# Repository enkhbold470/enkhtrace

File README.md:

# EnkhTrace V1.0

A line-follower robot board built around an STM32F103RET6, with a TB6612FNG
motor driver for two motors, a sensor-array header, a JDY-30 Bluetooth module,
an LY3200ALH gyro, a buzzer and status LEDs. Designed by Enkhbold Ganbold for
the Erdenet robot challenge.

| | |
|---|---|
| Size | 99.2 × 95.3 mm |
| Layers | 2 copper |
| Footprints | 82 |
| Nets | 87 |

## Files

- `hardware/enkhtrace.kicad_pcb` — the board in KiCad 10 format.
- `easyeda/enkhtrace_pcb.easyeda.json` — the original EasyEDA Standard document.
- `firmware/Src/` — the STM32 firmware (STM32CubeMX / HAL project sources).
- `images/` — a render of the top side, plus photos of the first build, the
  soldering and the bare PCB.

## Build photos

## Firmware

`firmware/Src/` holds the sources for the STM32F103RET6: `main.c` and the
STM32CubeMX-generated `stm32f1xx_hal_msp.c`, `stm32f1xx_it.c` and
`system_stm32f1xx.c`. It is the source folder only; the CubeMX project file,
the HAL/CMSIS drivers and the headers are not included, so regenerate them with
STM32CubeMX for an STM32F103RETx before building.

## Where it came from

The board was drawn in EasyEDA Standard and published on OSHWLab:
<https://oshwlab.com/enkhbold470/line-follower-for-erdenet-robot-challenge>.
It was converted with KiCad 10.0.6's EasyEDA importer and its copper pours were
refilled. With the pours filled, KiCad's DRC finds every net connected; the
remaining DRC findings are silkscreen and clearance checks against KiCad's
default rules, not the rules the board was designed to. No schematic was
published with the original project, so none is included.

## Licence

MIT — see [LICENSE](LICENSE) — for the board, the images and the code written
for this project. The STM32CubeMX-generated parts of the firmware are
© STMicroelectronics under the BSD 3-Clause licence stated in each file's
header, and those headers are kept as they were.

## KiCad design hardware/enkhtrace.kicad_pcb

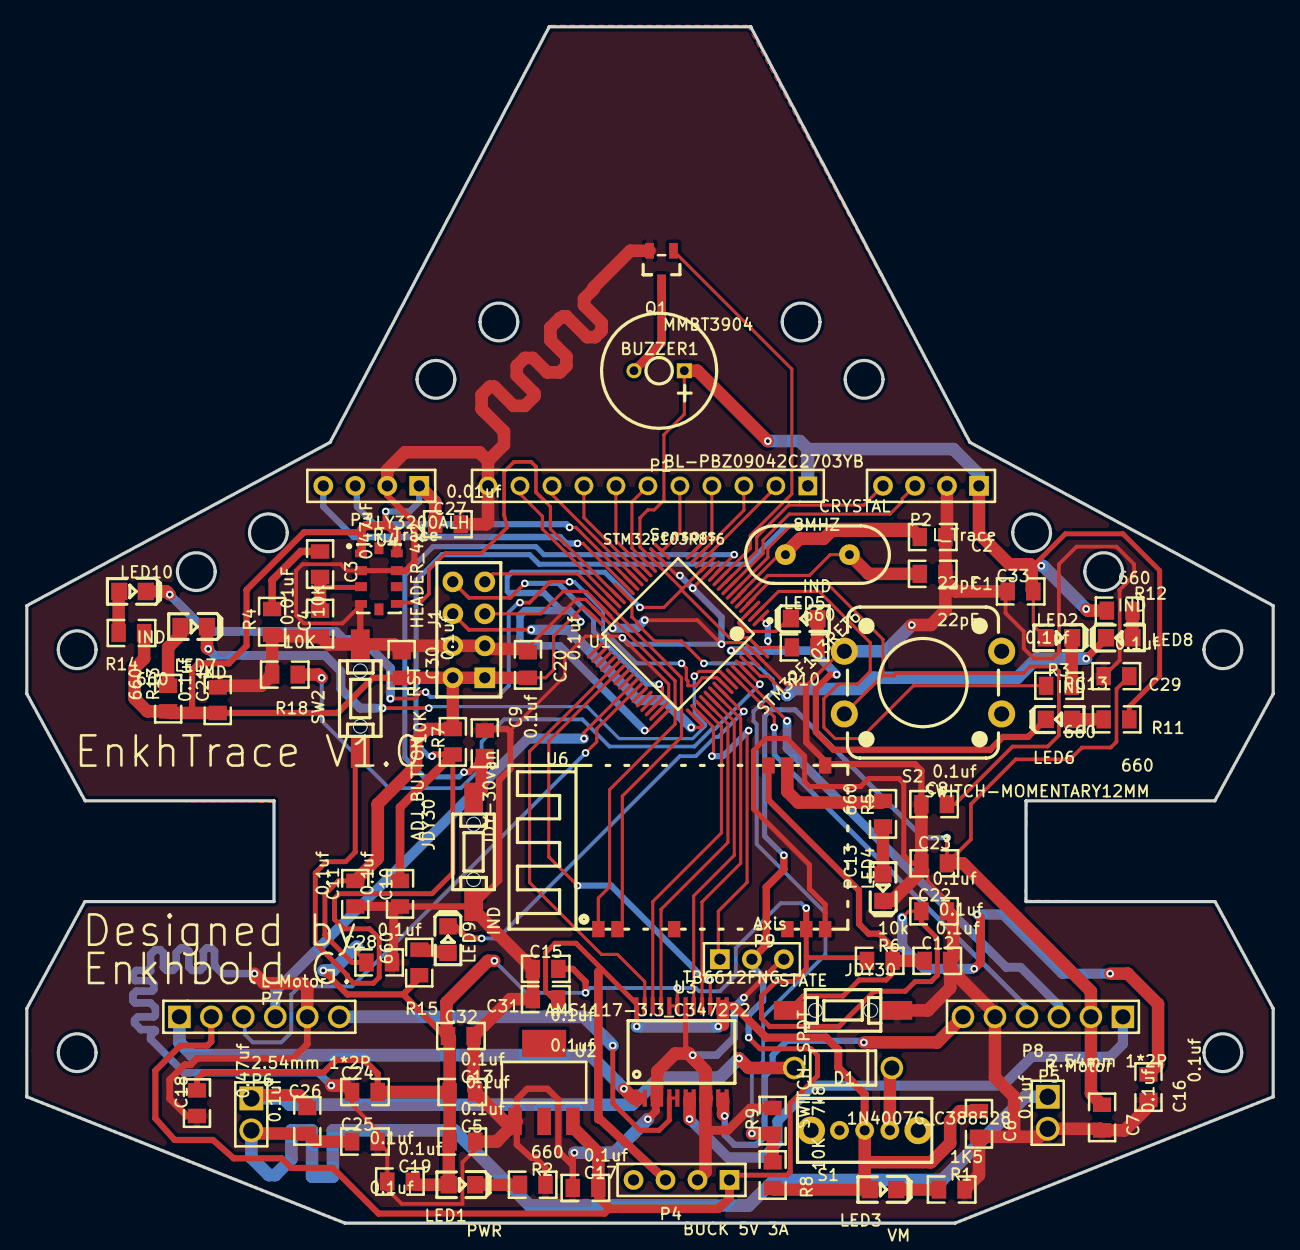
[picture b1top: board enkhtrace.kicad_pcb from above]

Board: 2 copper layers, 99.0 x 95.0 mm, 82 parts (0 on the bottom side), 70 nets.

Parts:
8MHZ: CRYSTAL; HC49US
ADJ_BUTTON: JDY30; SMD-6X3.3X5
BUZZER1: BL-PBZ09042C2703YB; BUZZER-R9.0-2P-4.0PITCH
C1, C2: 22pF; 0805
C3: 0.47uF; 0805
C4: 0.01uF; 0805
C5, C6, C7, C8, C9, C10, C11, C12, C13, C15, C16, C17, C19, C20, C21, C22, C23, C24, C25, C26, C28, C29, C30, C31, C32, C33: 0.1uf; 0805
C18: 0.47uf; 0805
C27: 0.01uf; 0805
D1: 1N4007G_C388528; DO-41_D1.20-L5.30-W2.80-L-RD
J1: HEADER_4x2; HEADER-2X4
LED1: PWR; LED-0805
LED2, LED4: PC13; LED-0805
LED3: VM; LED-0805
LED5, LED6, LED7, LED8, LED9, LED10: IND; LED-0805
P1: Sensors; HDR-11X1/2.54
P2: L_Trace; HDR-4X1/2.54
P3: R_Trace; HDR-4X1/2.54
P4: BUCK 5V 3A; HDR-4X1/2.54
P5, P6: 2.54mm 1*2P; HDR-2X1/2.54
P7: L Motor; HDR-6X1/2.54
P8: R Motor; HDR-6X1/2.54
P9: Axis; HDR-3X1/2.54
Q1: MMBT3904; SOT-23(SOT-23-3)
R1: 1K5; 0805
R2, R3, R5, R10, R11, R12, R13, R14, R15: 660; 0805
R4, R7, R8, R18: 10K; 0805
R6: 10k; 0805
R9: 7k8; 0805
S1: SWITCH-SPDT; SMD SWITCH 1234
S2: SWITCH-MOMENTARY12MM; TACTILE-PTH-12MM
STATE: JDY30; SMD-6X3.3X5
SW2: RST; SMD-6X3.3X5
U1: STM32F103RET6; LQFP-64_10X10X05P
U2: AMS1117-3.3_C347222; SOT-223
U3: TB6612FNG; SSOP24
U4: LY3200ALH; LGA10-3X5X1
U6: JDY-30van; JDY-30VAN-1.5-26.9X13.0X2.2MM

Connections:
+3V3: BUZZER1.1, C5.1, C11.2, C13.1, C15.1, C16.1, C18.1, C19.2, C20.2, C21.1, C22.1, C24.1, C27.1, C28.1, C30.2, C32.2, C33.1, J1.1, J1.2, LED1.1, LED2.1, P1.1, P2.1, P3.1, R6.1, R7.2, R10.1, R11.1, R12.1, R13.1, R14.1, R15.1, U1.1, U1.13, U1.19, U1.32, U1.48, U1.64, U3.19, U3.20, U4.1, U4.9, U6.12
+5V: C7.1, C17.2, C23.1, C29.2, P4.1, P7.2, P8.2, P9.2, U2.3
ADJ_BUTTON: ADJ_BUTTON.2, C9.2, U1.11
AIN1: U1.52, U3.21
AIN2: U1.51, U3.22
AXISPWM: P9.1, U1.50
BIN1: U1.53, U3.17
BIN2: U1.54, U3.16
BOOT0: R18.2, U1.60
BUZZ: Q1.1, U1.10
BUZZER1_2: BUZZER1.2, Q1.3
C3_1: C3.1, R4.1
GND: ADJ_BUTTON.1, C1.1, C2.1, C4.1, C5.2, C6.2, C7.2, C8.1, C9.1, C10.1, C11.1, C12.2, C13.2, C15.2, C16.2, C17.1, C18.2, C19.1, C20.1, C21.2, C22.2, C23.2, C24.2, C25.1, C27.2, C28.2, C29.1, C30.1, C31.2, C32.1, C33.2, J1.3, J1.4, LED4.2, P1.11, P2.2, P3.2, P4.2, P5.2, P7.5, P8.5, P9.3, Q1.2, R1.2, R2.2, R4.2, R9.1, R18.1, S2.1, STATE.2, SW2.1, U1.12, U1.18, U1.31, U1.47, U1.63, U2.1, U3.3, U3.4, U3.9, U3.10, U3.18, U4.2, U4.4, U4.8, U6.13, U6.22
GYROZ: U1.27, U4.6
IR: P1.10, U1.28
LCHA: P7.3, U1.42
LCHB: P7.4, U1.41
LED1: LED5.2, U1.3
LED1_2: LED1.2, R2.1
LED2: LED6.2, U1.62
LED2_2: LED2.2, R3.1
LED3: LED8.2, U1.61
LED3_2: LED3.2, R1.1
LED4: LED7.2, U1.57
LED5: LED10.2, U1.56
LED5_1: LED5.1, R10.2
LED6: LED9.2, U1.55
LED6_1: LED6.1, R11.2
LED7_1: LED7.1, R13.2
LED8_1: LED8.1, R12.2
LED9_1: LED9.1, R15.2
LED10_1: LED10.1, R14.2
ML1: P7.1, U3.1, U3.2
ML2: P7.6, U3.5, U3.6
MR1: P8.1, U3.7, U3.8
MR2: P8.6, U3.11, U3.12
P5_1: C25.2, C26.1, P5.1, P6.2
P6_1: C26.2, D1.2, P6.1
PC13: R3.2, U1.2
PWMA: U1.37, U3.23
PWMB: U1.38, U3.15
R5_1: LED4.1, R5.1
RCHA: P8.3, U1.59
RCHB: P8.4, U1.58
RST: C10.2, R7.1, SW2.2, U1.7
RX: J1.5, U1.30, U6.1
S1_2: D1.1, S1.2
SENSOR1: P1.2, U1.14
SENSOR2: P1.3, U1.15
SENSOR3: P1.4, U1.16
SENSOR4: P1.5, U1.17
SENSOR5: P1.6, U1.20
SENSOR6: P1.7, U1.21
SENSOR7: P1.8, U1.22
SENSOR8: P1.9, U1.23
START: C8.2, S2.3, U1.4
SWCLK: J1.6, U1.49
SWDIO: J1.8, U1.46
TRACE1: P2.3, U1.8
TRACE2: P2.4, U1.9
TRACE3: P3.3, U1.24
TRACE4: P3.4, U1.25
TX: J1.7, U1.29, U6.2
U1_5: 8MHZ.2, C1.2, U1.5
U1_6: 8MHZ.1, C2.2, U1.6
U4_3: C3.2, C4.2, U4.3
U6_24: R5.2, U6.24
U6_25: C12.1, R6.2, STATE.1, U6.25
VM: C6.1, C31.1, LED3.1, P4.3, R8.2, S1.1, U3.13, U3.14, U3.24
VOLTMETER: R8.1, R9.2, U1.26

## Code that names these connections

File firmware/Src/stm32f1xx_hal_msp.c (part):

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    PC4     ------> ADC1_IN14
    PC5     ------> ADC1_IN15 
    */
    GPIO_InitStruct.Pin = TRACE1_Pin|TRACE2_Pin|TRACE3_Pin|TRACE4_Pin;
    GPIO_InitStruct.Mode = GPIO_MODE_ANALOG;
    HAL_GPIO_Init(GPIOC, &GPIO_InitStruct);

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    /**ADC2 GPIO Configuration    
    PB0     ------> ADC2_IN8 
    */
    GPIO_InitStruct.Pin = Voltmeter_Pin;
    GPIO_InitStruct.Mode = GPIO_MODE_ANALOG;
    HAL_GPIO_Init(Voltmeter_GPIO_Port, &GPIO_InitStruct);

  /* USER CODE BEGIN ADC2_MspInit 1 */

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    PC4     ------> ADC1_IN14
    PC5     ------> ADC1_IN15 
    */
    HAL_GPIO_DeInit(GPIOC, TRACE1_Pin|TRACE2_Pin|TRACE3_Pin|TRACE4_Pin);

    HAL_GPIO_DeInit(GPIOA, S1_Pin|S2_Pin|S3_Pin|S4_Pin 
                          |S5_Pin|S6_Pin);
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    /**ADC2 GPIO Configuration    
    PB0     ------> ADC2_IN8 
    */
    HAL_GPIO_DeInit(Voltmeter_GPIO_Port, Voltmeter_Pin);

  /* USER CODE BEGIN ADC2_MspDeInit 1 */

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    PA8     ------> TIM1_CH1
    PA9     ------> TIM1_CH2 
    */
    GPIO_InitStruct.Pin = LCHB_Pin|LCHA_Pin;
    GPIO_InitStruct.Mode = GPIO_MODE_INPUT;
    GPIO_InitStruct.Pull = GPIO_NOPULL;
    HAL_GPIO_Init(GPIOA, &GPIO_InitStruct);
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    PB6     ------> TIM4_CH1
    PB7     ------> TIM4_CH2 
    */
    GPIO_InitStruct.Pin = RCHB_Pin|RCHA_Pin;
    GPIO_InitStruct.Mode = GPIO_MODE_INPUT;
    GPIO_InitStruct.Pull = GPIO_NOPULL;
    HAL_GPIO_Init(GPIOB, &GPIO_InitStruct);
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    /**TIM2 GPIO Configuration    
    PA15     ------> TIM2_CH1 
    */
    GPIO_InitStruct.Pin = AxisPWM_Pin;
    GPIO_InitStruct.Mode = GPIO_MODE_AF_PP;
    GPIO_InitStruct.Speed = GPIO_SPEED_FREQ_LOW;
    HAL_GPIO_Init(AxisPWM_GPIO_Port, &GPIO_InitStruct);

    __HAL_AFIO_REMAP_TIM2_PARTIAL_1();

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    PC6     ------> TIM3_CH1
    PC7     ------> TIM3_CH2 
    */
    GPIO_InitStruct.Pin = PWMB_Pin|PWMA_Pin;
    GPIO_InitStruct.Mode = GPIO_MODE_AF_PP;
    GPIO_InitStruct.Speed = GPIO_SPEED_FREQ_LOW;
    HAL_GPIO_Init(GPIOC, &GPIO_InitStruct);
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    PA8     ------> TIM1_CH1
    PA9     ------> TIM1_CH2 
    */
    HAL_GPIO_DeInit(GPIOA, LCHB_Pin|LCHA_Pin);

  /* USER CODE BEGIN TIM1_MspDeInit 1 */

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    PB6     ------> TIM4_CH1
    PB7     ------> TIM4_CH2 
    */
    HAL_GPIO_DeInit(GPIOB, RCHB_Pin|RCHA_Pin);

  /* USER CODE BEGIN TIM4_MspDeInit 1 */

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
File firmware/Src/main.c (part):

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
void Motor(int R, int L){
	if(R>0){
		  HAL_GPIO_WritePin(AIN1_GPIO_Port,AIN1_Pin,GPIO_PIN_SET);
			HAL_GPIO_WritePin(AIN2_GPIO_Port,AIN2_Pin,GPIO_PIN_RESET);
	}else
	if(R<0){
//      L=L*(-1);	   
		  HAL_GPIO_WritePin(AIN1_GPIO_Port,AIN1_Pin,GPIO_PIN_RESET);
			HAL_GPIO_WritePin(AIN2_GPIO_Port,AIN2_Pin,GPIO_PIN_SET);
	}else{
			HAL_GPIO_WritePin(BIN1_GPIO_Port,BIN1_Pin,GPIO_PIN_SET);
			HAL_GPIO_WritePin(BIN2_GPIO_Port,BIN2_Pin,GPIO_PIN_SET);
	}
	
	
	
	if(L>0){
		  HAL_GPIO_WritePin(BIN1_GPIO_Port,BIN1_Pin,GPIO_PIN_SET);
			HAL_GPIO_WritePin(BIN2_GPIO_Port,BIN2_Pin,GPIO_PIN_RESET);
	}else
	if(L<0){
//		  R=R*(-1);
		  HAL_GPIO_WritePin(BIN1_GPIO_Port,BIN1_Pin,GPIO_PIN_RESET);
			HAL_GPIO_WritePin(BIN2_GPIO_Port,BIN2_Pin,GPIO_PIN_SET);
	}else
	{
			HAL_GPIO_WritePin(BIN1_GPIO_Port,BIN1_Pin,GPIO_PIN_SET);
			HAL_GPIO_WritePin(BIN2_GPIO_Port,BIN2_Pin,GPIO_PIN_SET);
	}

	
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HAL_GPIO_WritePin(Hiz_test_GPIO_Port,Hiz_test_Pin,GPIO_PIN_RESET);

	
		 HAL_GPIO_WritePin(BUZZ_GPIO_Port,BUZZ_Pin,GPIO_PIN_SET);
	
	}else{
	 HAL_GPIO_WritePin(BUZZ_GPIO_Port,BUZZ_Pin,GPIO_PIN_RESET);
	 
HAL_GPIO_WritePin(Hiz_test_GPIO_Port,Hiz_test_Pin,GPIO_PIN_SET);
	}
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
void buzzer(int count){
		for(int i=0;i<count;i++){
			 HAL_GPIO_WritePin(BUZZ_GPIO_Port,BUZZ_Pin,GPIO_PIN_SET);
			HAL_Delay(50);
			 HAL_GPIO_WritePin(BUZZ_GPIO_Port,BUZZ_Pin,GPIO_PIN_RESET);
			HAL_Delay(50);
		}
		
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	
void buzzer_notes(int count, int time){
		for(int i=0;i<count;i++){
			 HAL_GPIO_WritePin(BUZZ_GPIO_Port,BUZZ_Pin,GPIO_PIN_SET);
			HAL_Delay(time);
			 HAL_GPIO_WritePin(BUZZ_GPIO_Port,BUZZ_Pin,GPIO_PIN_RESET);
			HAL_Delay(time);
		}
		
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  __HAL_RCC_GPIOB_CLK_ENABLE();

  /*Configure GPIO pin Output Level */
  HAL_GPIO_WritePin(GPIOC, Hde_test_Pin|BUZZ_Pin|AIN2_Pin|AIN1_Pin 
                          |BIN1_Pin, GPIO_PIN_RESET);

  /*Configure GPIO pin Output Level */
  HAL_GPIO_WritePin(BIN2_GPIO_Port, BIN2_Pin, GPIO_PIN_RESET);

  /*Configure GPIO pin Output Level */
  HAL_GPIO_WritePin(GPIOB, BAT_LED_Pin|Hiz_test_Pin|MODE_Pin, GPIO_PIN_RESET);

  /*Configure GPIO pins : Hde_test_Pin BUZZ_Pin AIN2_Pin AIN1_Pin 
                           BIN1_Pin */
  GPIO_InitStruct.Pin = Hde_test_Pin|BUZZ_Pin|AIN2_Pin|AIN1_Pin 
                          |BIN1_Pin;
  GPIO_InitStruct.Mode = GPIO_MODE_OUTPUT_PP;
  GPIO_InitStruct.Speed = GPIO_SPEED_FREQ_LOW;
  HAL_GPIO_Init(GPIOC, &GPIO_InitStruct);
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  GPIO_InitStruct.Pull = GPIO_PULLDOWN;
  HAL_GPIO_Init(STOP_SENSOR_GPIO_Port, &GPIO_InitStruct);

  /*Configure GPIO pin : BIN2_Pin */
  GPIO_InitStruct.Pin = BIN2_Pin;
  GPIO_InitStruct.Mode = GPIO_MODE_OUTPUT_PP;
  GPIO_InitStruct.Speed = GPIO_SPEED_FREQ_LOW;
  HAL_GPIO_Init(BIN2_GPIO_Port, &GPIO_InitStruct);

  /*Configure GPIO pins : BAT_LED_Pin Hiz_test_Pin MODE_Pin */
  GPIO_InitStruct.Pin = BAT_LED_Pin|Hiz_test_Pin|MODE_Pin;
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

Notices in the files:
firmware/Src/main.c:
COPYRIGHT(c) 2019 STMicroelectronics
(C) COPYRIGHT STMicroelectronics *****END OF FILE
